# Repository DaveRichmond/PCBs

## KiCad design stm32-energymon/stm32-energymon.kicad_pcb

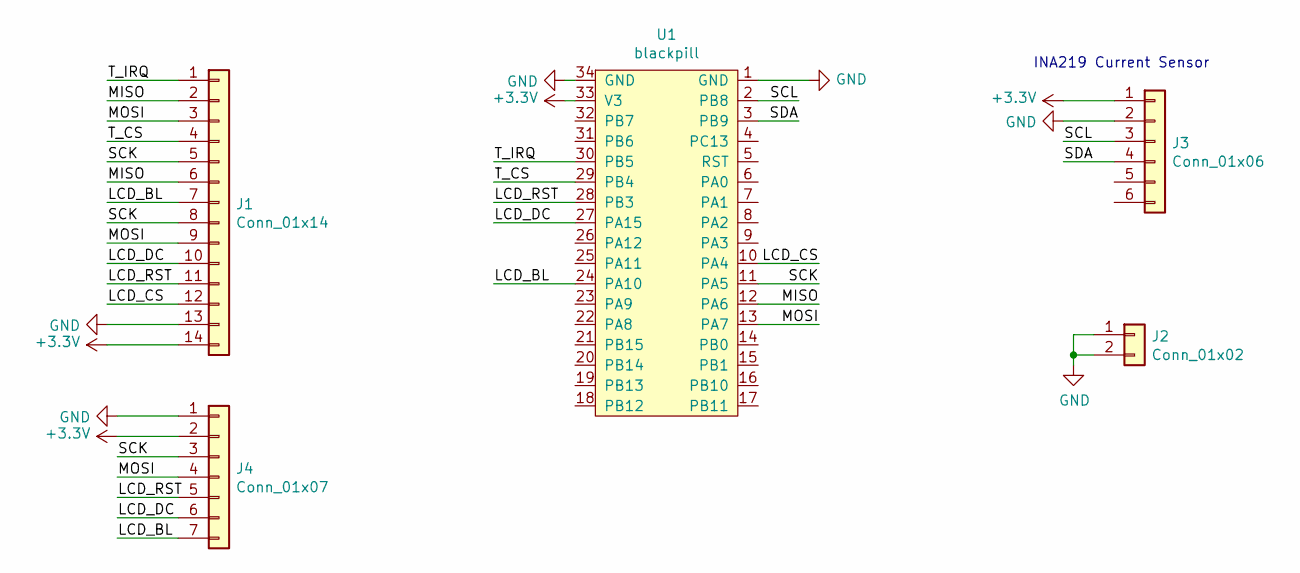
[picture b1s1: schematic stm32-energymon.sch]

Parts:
J1: Conn_01x14; PinSocket_1x14_P2.54mm_Vertical
J2: Conn_01x02; TerminalBlock_bornier-2_P5.08mm
J3: Conn_01x06; PinSocket_1x06_P2.54mm_Vertical
J4: Conn_01x07; PinSocket_1x07_P2.54mm_Vertical
U1: blackpill

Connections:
+3V3: J1.14, J3.1, J4.2, U1.33 (V3)
/LCD_BL: J1.7, J4.7, U1.24 (PA10)
/LCD_CS: J1.12, U1.10 (PA4)
/LCD_DC: J1.10, J4.6, U1.27 (PA15)
/LCD_RST: J1.11, J4.5, U1.28 (PB3)
/MISO: J1.2, J1.6, U1.12 (PA6)
/MOSI: J1.3, J1.9, J4.4, U1.13 (PA7)
/SCK: J1.5, J1.8, J4.3, U1.11 (PA5)
/SCL: J3.3, U1.2 (PB8)
/SDA: J3.4, U1.3 (PB9)
/T_CS: J1.4, U1.29 (PB4)
/T_IRQ: J1.1, U1.30 (PB5)
GND: J1.13, J2.1, J2.2, J3.2, J4.1, U1.1 (GND), U1.34 (GND)

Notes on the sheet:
INA219 Current Sensor

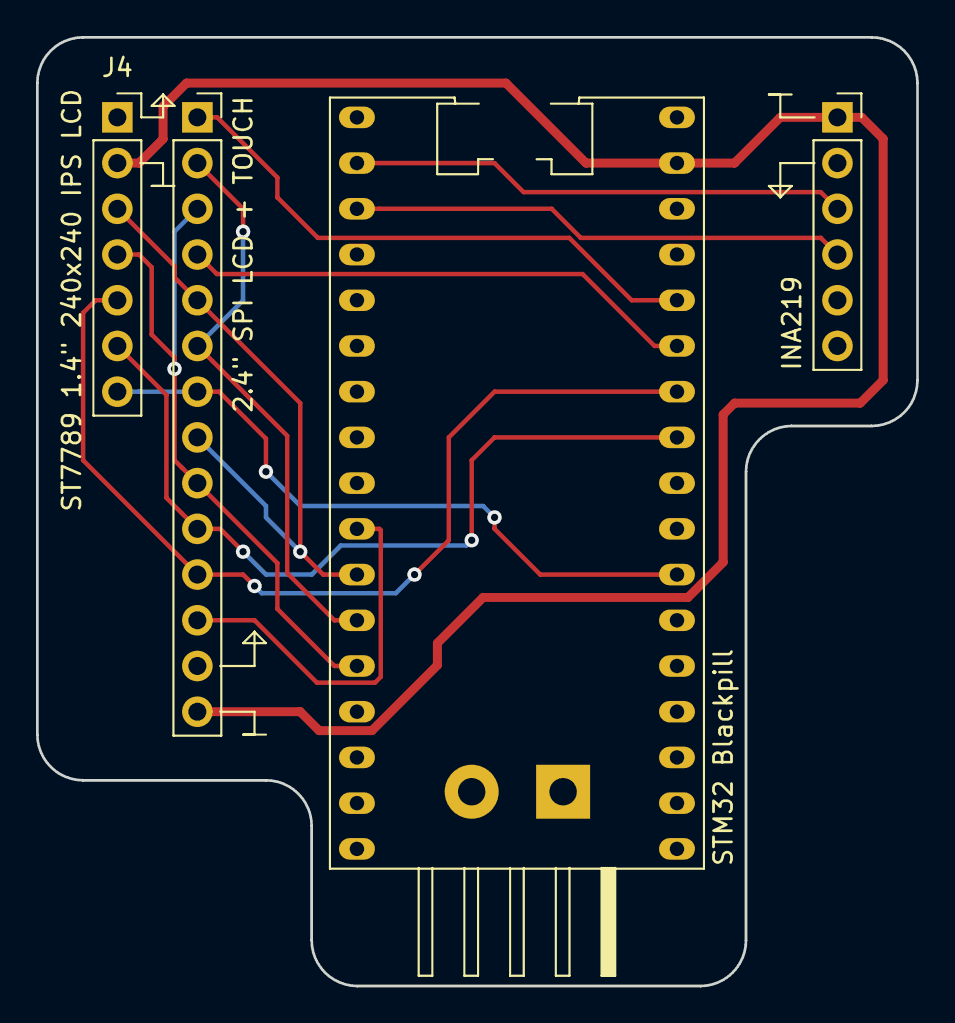
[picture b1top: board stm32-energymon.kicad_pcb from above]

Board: 2 copper layers, 48.9 x 52.7 mm, 5 parts (1 on the bottom side), 13 nets.
